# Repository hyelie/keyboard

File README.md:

# keyboard
repository for both-side-B reversed-tenkey hotswap split keyboard

## directory description
```
├─firmware
│  ├─hyelie - QMK firmware folder
│  └─kbfirmware - kbfirmware layout folder (for reference)
├─PCB
│  ├─gerber - my gerber file folder
│  └─lib - Kicad library folder
├─housing - 3D CAD folder for housing
├─specification - specifications
└─제작기 - manufacturing guide
```

## manufacturing guide

[키보드 제작기 1편. 왼쪽 PCB 설계](./%EC%A0%9C%EC%9E%91%EA%B8%B0/1.%20%EC%99%BC%EC%AA%BD%20pcb/README.md)

[키보드 제작기 2편. 양쪽 PCB 완성 및 주문](./%EC%A0%9C%EC%9E%91%EA%B8%B0/2.%20%EC%96%91%EC%AA%BD%20PCB%20%EC%99%84%EC%84%B1%20%EB%B0%8F%20%EC%A3%BC%EB%AC%B8/README.md)

[키보드 제작기 3편. 납땜 & 펌웨어 올리기](./제작기/3.%20납땜%20&%20펌웨어/README.md)

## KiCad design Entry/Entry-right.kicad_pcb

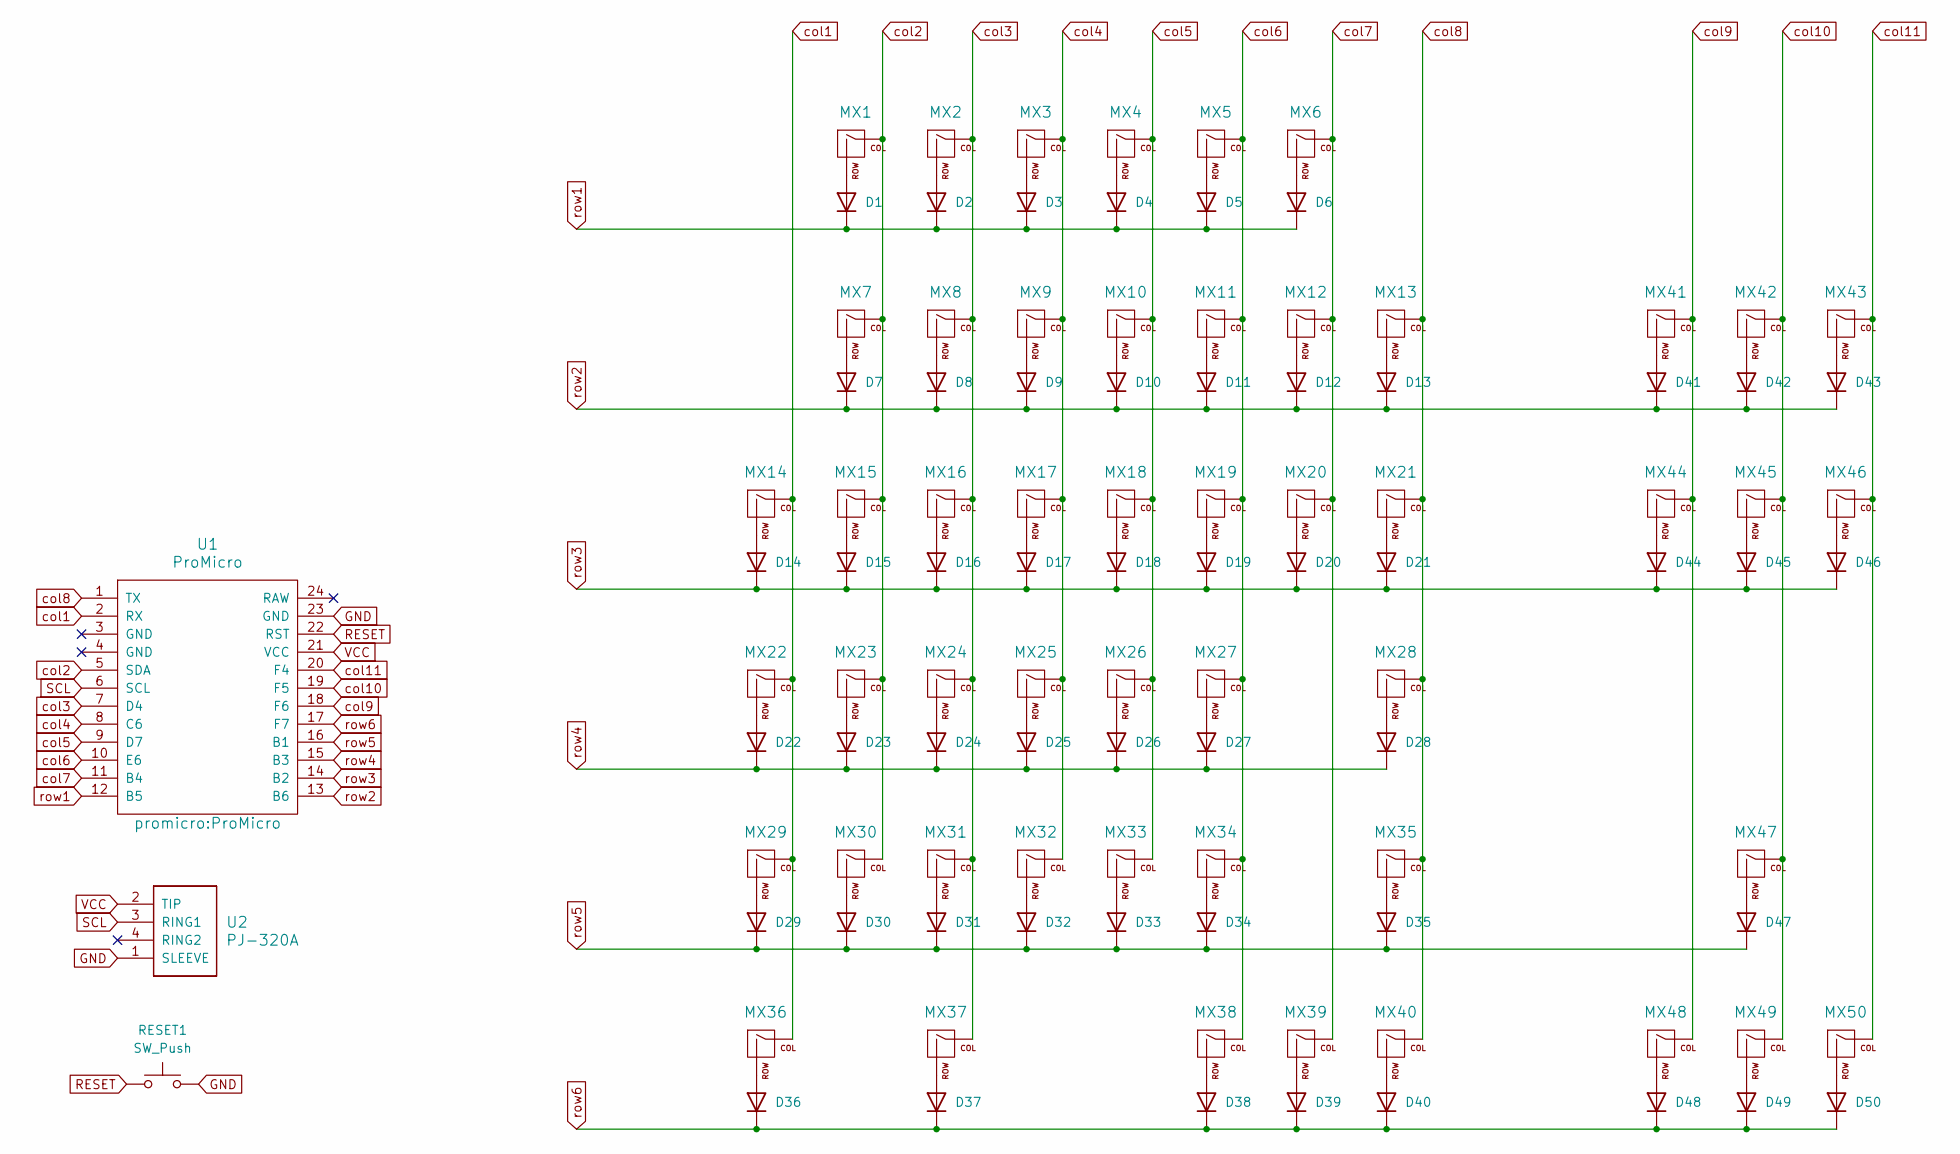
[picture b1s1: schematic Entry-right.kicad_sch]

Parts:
D1, D2, D3, D4, D5, D6, D7, D8, D9, D10, D11, D12, D13, D14, D15, D16, D17, D18, D19, D20, D21, D22, D23, D24, D25, D26, D27, D28, D29, D30, D31, D32, D33, D34, D35, D36, D37, D38, D39, D40, D41, D42, D43, D44, D45, D46, D47, D48, D49, D50: 1N4148; D_DO-35_SOD27_P7.62mm_Horizontal
MX1, MX2, MX3, MX4, MX5, MX6, MX7, MX8, MX9, MX10, MX11, MX12, MX14, MX15, MX16, MX17, MX18, MX19, MX20, MX22, MX23, MX24, MX25, MX26, MX27, MX29, MX30, MX31, MX32, MX33, MX34, MX37, MX41, MX42, MX43, MX44, MX45, MX46, MX47, MX48, MX49, MX50: MX-NoLED; MXOnly-1U-Hotswap
MX13, MX36: MX-NoLED; MXOnly-2U-Hotswap
MX21: MX-NoLED; MXOnly-1.5U-Hotswap
MX28: MX-NoLED; MXOnly-2.25U-Hotswap
MX35: MX-NoLED; MXOnly-2.75U-Hotswap
MX38, MX39, MX40: MX-NoLED; MXOnly-1.25U-Hotswap
RESET1: SW_Push; ResetSW_4P
U1: ProMicro
U2: PJ-320A; TRRS-PJ-320A

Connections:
GND: RESET1.2, U1.23 (GND), U2.1 (SLEEVE)
unnamed: D1.2 (A), MX1.2 (ROW)
unnamed: D2.2 (A), MX2.2 (ROW)
unnamed: D3.2 (A), MX3.2 (ROW)
unnamed: D4.2 (A), MX4.2 (ROW)
unnamed: D5.2 (A), MX5.2 (ROW)
unnamed: D6.2 (A), MX6.2 (ROW)
unnamed: D7.2 (A), MX7.2 (ROW)
unnamed: D8.2 (A), MX8.2 (ROW)
unnamed: D9.2 (A), MX9.2 (ROW)
unnamed: D10.2 (A), MX10.2 (ROW)
unnamed: D11.2 (A), MX11.2 (ROW)
unnamed: D12.2 (A), MX12.2 (ROW)
unnamed: D13.2 (A), MX13.2 (ROW)
unnamed: D14.2 (A), MX14.2 (ROW)
unnamed: D15.2 (A), MX15.2 (ROW)
unnamed: D16.2 (A), MX16.2 (ROW)
unnamed: D17.2 (A), MX17.2 (ROW)
unnamed: D18.2 (A), MX18.2 (ROW)
unnamed: D19.2 (A), MX19.2 (ROW)
unnamed: D20.2 (A), MX20.2 (ROW)
unnamed: D21.2 (A), MX21.2 (ROW)
unnamed: D22.2 (A), MX22.2 (ROW)
unnamed: D23.2 (A), MX23.2 (ROW)
unnamed: D24.2 (A), MX24.2 (ROW)
unnamed: D25.2 (A), MX25.2 (ROW)
unnamed: D26.2 (A), MX26.2 (ROW)
unnamed: D27.2 (A), MX27.2 (ROW)
unnamed: D28.2 (A), MX28.2 (ROW)
unnamed: D29.2 (A), MX29.2 (ROW)
unnamed: D30.2 (A), MX30.2 (ROW)
unnamed: D31.2 (A), MX31.2 (ROW)
unnamed: D32.2 (A), MX32.2 (ROW)
unnamed: D33.2 (A), MX33.2 (ROW)
unnamed: D34.2 (A), MX34.2 (ROW)
unnamed: D35.2 (A), MX35.2 (ROW)
unnamed: D36.2 (A), MX36.2 (ROW)
unnamed: D37.2 (A), MX37.2 (ROW)
unnamed: D38.2 (A), MX38.2 (ROW)
unnamed: D39.2 (A), MX39.2 (ROW)
unnamed: D40.2 (A), MX40.2 (ROW)
unnamed: D41.2 (A), MX41.2 (ROW)
unnamed: D42.2 (A), MX42.2 (ROW)
unnamed: D43.2 (A), MX43.2 (ROW)
unnamed: D44.2 (A), MX44.2 (ROW)
unnamed: D45.2 (A), MX45.2 (ROW)
unnamed: D46.2 (A), MX46.2 (ROW)
unnamed: D47.2 (A), MX47.2 (ROW)
unnamed: D48.2 (A), MX48.2 (ROW)
unnamed: D49.2 (A), MX49.2 (ROW)
unnamed: D50.2 (A), MX50.2 (ROW)
RESET: RESET1.1, U1.22 (RST)
SCL: U1.6 (SCL), U2.3 (RING1)
VCC: U1.21 (VCC), U2.2 (TIP)
col1: MX14.1 (COL), MX22.1 (COL), MX29.1 (COL), MX36.1 (COL), U1.2 (RX)
col2: MX1.1 (COL), MX7.1 (COL), MX15.1 (COL), MX23.1 (COL), MX30.1 (COL), U1.5 (SDA)
col3: MX2.1 (COL), MX8.1 (COL), MX16.1 (COL), MX24.1 (COL), MX31.1 (COL), MX37.1 (COL), U1.7 (D4)
col4: MX3.1 (COL), MX9.1 (COL), MX17.1 (COL), MX25.1 (COL), MX32.1 (COL), U1.8 (C6)
col5: MX4.1 (COL), MX10.1 (COL), MX18.1 (COL), MX26.1 (COL), MX33.1 (COL), U1.9 (D7)
col6: MX5.1 (COL), MX11.1 (COL), MX19.1 (COL), MX27.1 (COL), MX34.1 (COL), MX38.1 (COL), U1.10 (E6)
col7: MX6.1 (COL), MX12.1 (COL), MX20.1 (COL), MX39.1 (COL), U1.11 (B4)
col8: MX13.1 (COL), MX21.1 (COL), MX28.1 (COL), MX35.1 (COL), MX40.1 (COL), U1.1 (TX)
col9: MX41.1 (COL), MX44.1 (COL), MX48.1 (COL), U1.18 (F6)
col10: MX42.1 (COL), MX45.1 (COL), MX47.1 (COL), MX49.1 (COL), U1.19 (F5)
col11: MX43.1 (COL), MX46.1 (COL), MX50.1 (COL), U1.20 (F4)
row1: D1.1 (K), D2.1 (K), D3.1 (K), D4.1 (K), D5.1 (K), D6.1 (K), U1.12 (B5)
row2: D7.1 (K), D8.1 (K), D9.1 (K), D10.1 (K), D11.1 (K), D12.1 (K), D13.1 (K), D41.1 (K), D42.1 (K), D43.1 (K), U1.13 (B6)
row3: D14.1 (K), D15.1 (K), D16.1 (K), D17.1 (K), D18.1 (K), D19.1 (K), D20.1 (K), D21.1 (K), D44.1 (K), D45.1 (K), D46.1 (K), U1.14 (B2)
row4: D22.1 (K), D23.1 (K), D24.1 (K), D25.1 (K), D26.1 (K), D27.1 (K), D28.1 (K), U1.15 (B3)
row5: D29.1 (K), D30.1 (K), D31.1 (K), D32.1 (K), D33.1 (K), D34.1 (K), D35.1 (K), D47.1 (K), U1.16 (B1)
row6: D36.1 (K), D37.1 (K), D38.1 (K), D39.1 (K), D40.1 (K), D48.1 (K), D49.1 (K), D50.1 (K), U1.17 (F7)

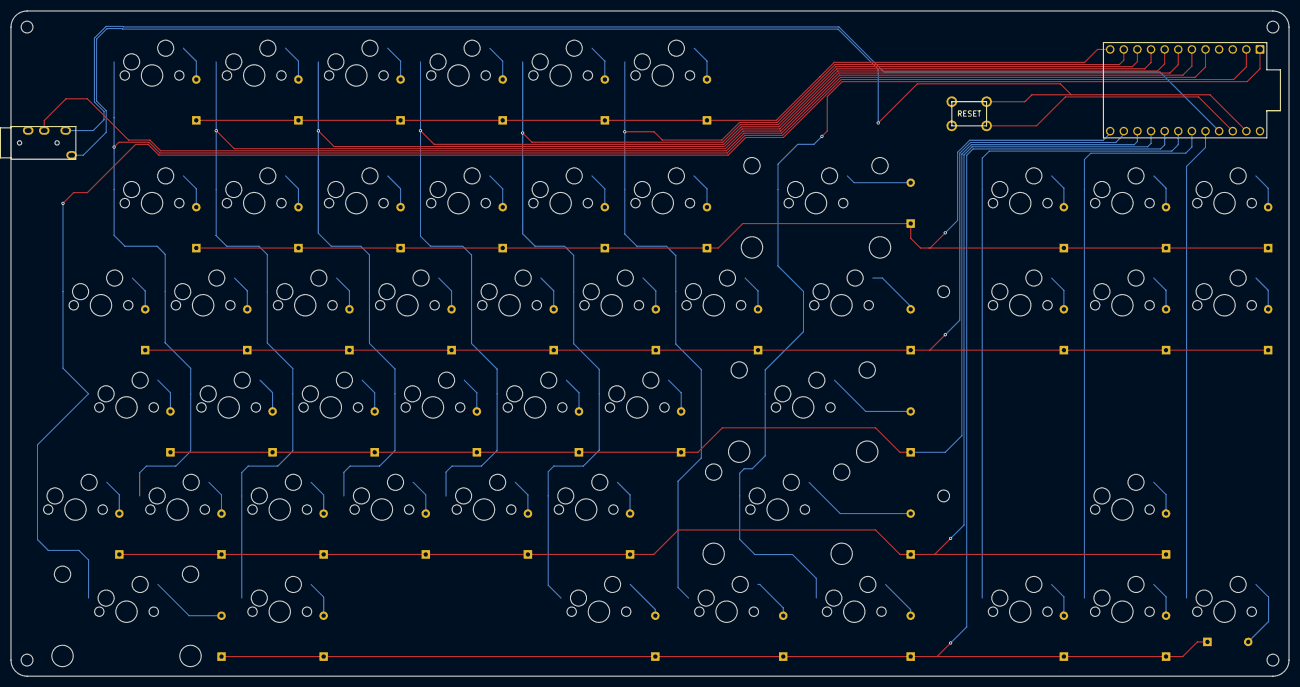
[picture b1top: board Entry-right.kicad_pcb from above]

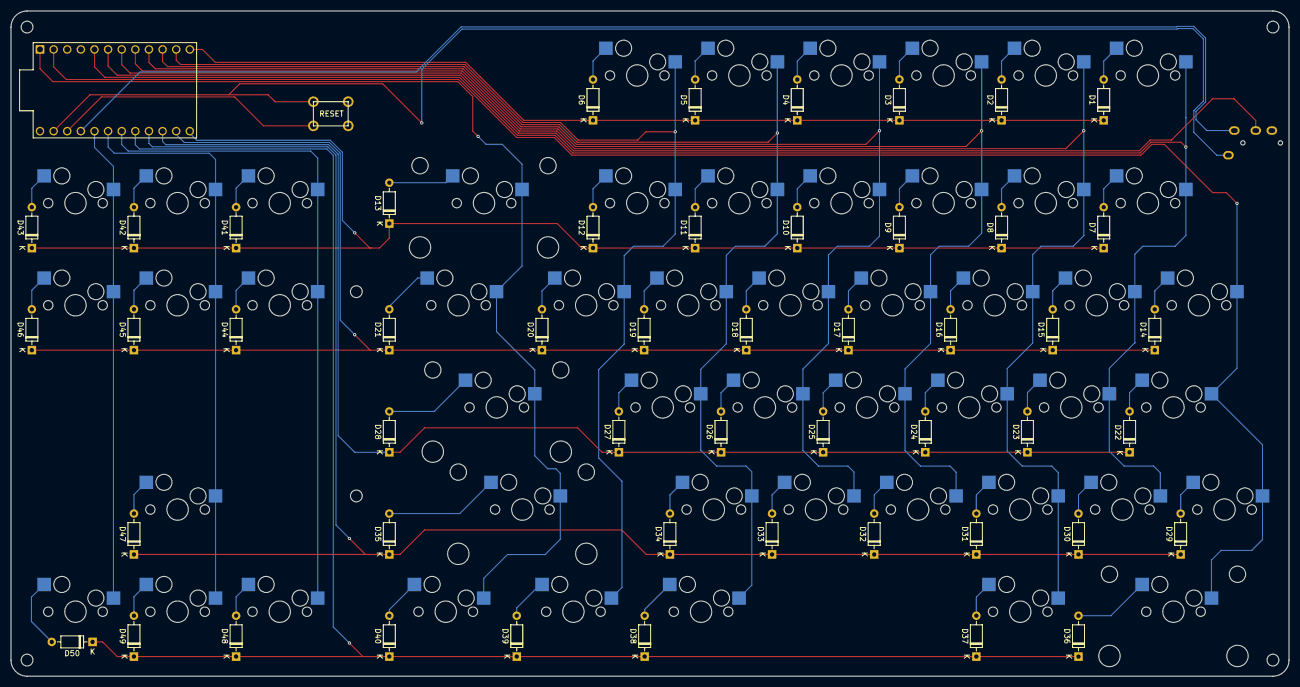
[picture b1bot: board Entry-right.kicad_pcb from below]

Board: 2 copper layers, 238.4 x 124.1 mm, 103 parts (50 on the bottom side), 71 nets.

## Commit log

2023-06-14 Add: left keyboard pcb and circuit
2023-06-14 docs: Add report 1
2023-06-14 docs: Edit Readme
2023-06-14 docs: 제작기 텍스트 파일 readme로 변경
2023-06-17 Add: reversed numberpad
2023-06-17 Add: plate by generator
2023-06-19 Fix: relocated left PCB wire more tight
2023-06-19 Add: right PCB
2023-06-22 Fix: draw both PCB outline & rename 1. rename project name from 'bottom-up' to 'Entry' 2. removed unused backup files 3. fix both PCB outline - margin 2.5mm, round 3mm 4. made gerber files
2023-06-23 docs: write main readme
2023-06-23 docs: Add manufacturing process 2
2023-06-23 docs: Edit manufacturing process 1 - Add object
2023-06-23 docs: Edit main readme
2023-06-23 docs: Edit manufacturing process 1 - make bold font on highlights
2023-06-23 docs: Edit manufacturing process 2 - edit bolt font on highlights & fix typos
2023-06-23 docs: Edit manufacturing process 1 - Fix reference view error
2023-07-04 docs: Edit manufacturing process 3 - housing informantions
2023-07-05 Add: Get left firmware from kbfirmware.com
2023-07-06 Add: CAD library & specifications
2023-07-06 Add: gitignore file
2023-07-08 Docs: rename 3.하우징 to 4.하우징
2023-07-08 Rename: rename Entry to PCB
2023-07-08 docs: move specification files
2023-07-08 Add: firmware files
2023-07-08 Docs: write manufacturing report 3. 납땜 & 펌웨어 제작기
2023-07-08 docs: Append manufacturing process 3 link into main readme
2023-07-08 Rename: rename from plate to housing
2023-07-08 docs: Append directory description into main readme
2023-07-08 Remove: remove unused files
2023-07-08 docs: Fix type in manufacturing guide 3
2023-07-08 docs: add result picture in manufacturing guide & add bold
2023-07-17 Add: add esdf and ijkl arrow feature
2023-08-16 Sync: Append housing database files
2023-09-01 add: Append housing result step files
2023-10-24 fix: Add backspace & remove key to right space
2024-01-07 Add: Append MACOS key mapping
2024-04-19 feat: Apply OS detection & Remove OS-dependent keymaps
2024-04-19 docs: Append os detection
2024-08-29 fix: Fix OS detection not work
2024-08-29 fix: Switch option and command key on MACOS
